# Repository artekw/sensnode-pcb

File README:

you need EAGLE 6.3.0 to open files

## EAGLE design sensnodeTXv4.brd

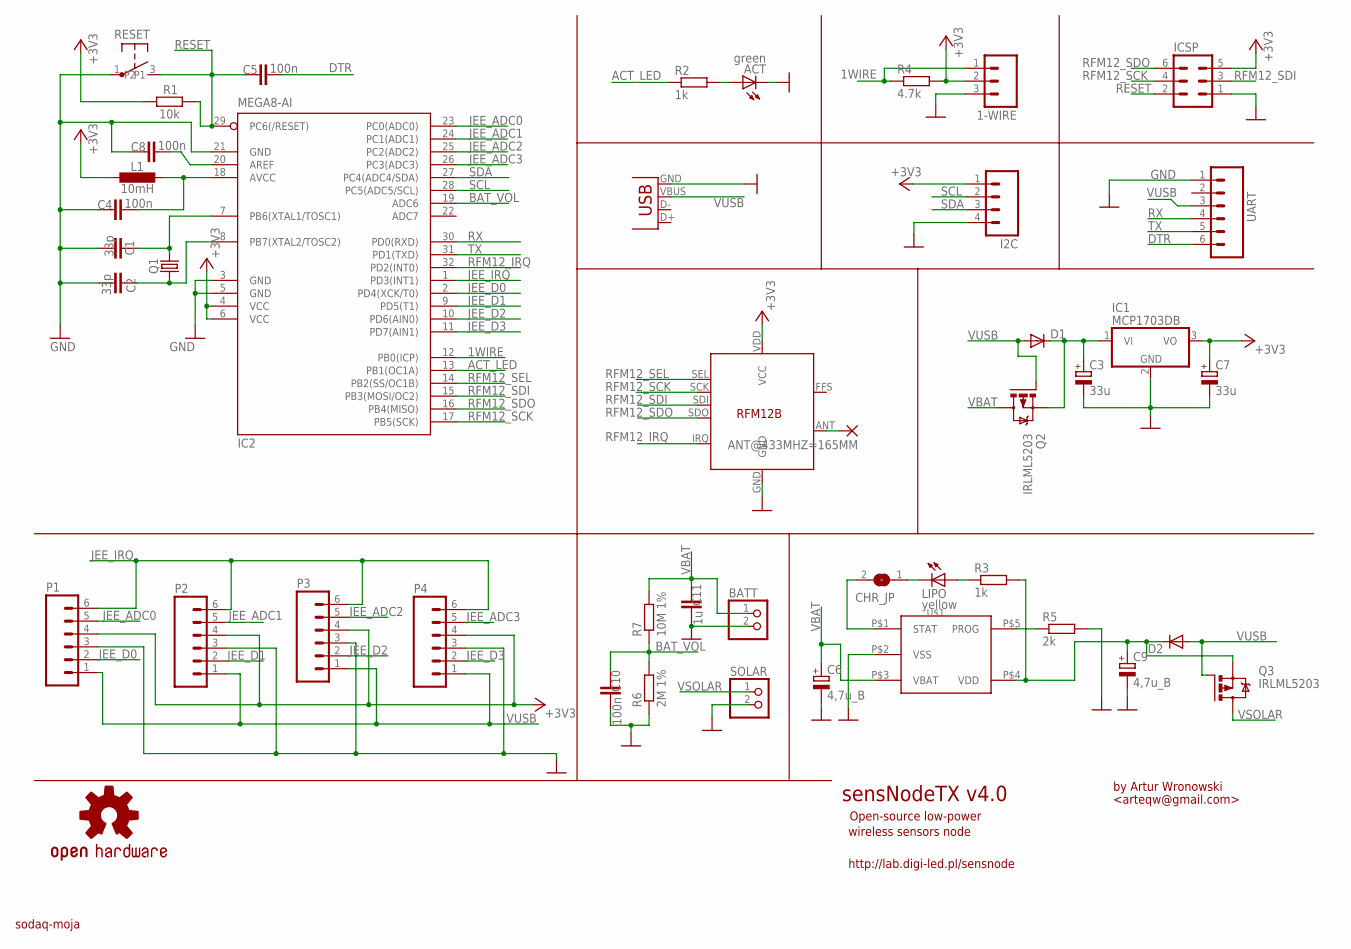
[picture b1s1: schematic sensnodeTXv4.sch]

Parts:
1-WIRE: M03LOCK; 1X03_LOCK
ACT: green; 1206
ANT@433MHZ=165MM: 2,15/1,0
BATT: PINHD-1X2; 1X02
C1, C2: 33p; C0805
C3, C7: 33u; SMC_B
C4, C5, C8, C10: 100n; C0805
C6, C9: 4,7u_B; SMC_B
C11: 1u; C0805
CHR_JP: JUMPER; SJW
D1, D2: 1n5819 melf; MELF-MLL41
I2C: M04LOCK; 1X04_LOCK
IC1: MCP1703DB; SOT223
IC2: MEGA8-AI; TQFP32-08
ICSP: MA03-2
L1: 10mH; 0207/7
LIPO: yellow; 1206
P1, P2, P3, P4: M06SIP_LOCK; 1X06-SIP_LOCK
Q1: CRYSTALHC49U70; HC49U70
Q2, Q3: IRLML5203; MICRO3
R1: 10k; M0805
R2, R3: 1k; M0805
R4: 4.7k; M0805
R5: 2k; M0805
R6: 2M 1%; M0805
R7: 10M 1%; M0805
RESET: TACT3X6; TACK3X6
RFM12B: RFM12B
SOLAR: PINHD-1X2; 1X02
U$1: MCP73831; 5PIN_SOT23
U$3: OSHW-LOGOM; OSHW-LOGO-M
UART: M06SIP_LOCK; 1X06-SIP_LOCK
USB_PWR: USBSMD; USB-MINIB

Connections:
1WIRE: 1-WIRE.1, IC2.12 (PB0(ICP)), R4.1
+3V3: 1-WIRE.2, C7.+, I2C.1, IC1.3 (VO), IC2.4 (VCC), IC2.6 (VCC), ICSP.5, L1.1, P1.4, P2.4, P3.4, P4.4, R1.1, R4.2, RFM12B.VDD (VCC)
ACT_LED: IC2.13 (PB1(OC1A)), R2.1
BAT_VOL: C10.2, IC2.19 (ADC6), R6.2, R7.1
DTR: C5.1, UART.6
GND: 1-WIRE.3, ACT.C, BATT.2, C1.2, C2.2, C3.-, C4.2, C6.-, C7.-, C8.2, C9.-, C10.1, C11.1, I2C.4, IC1.2 (GND), IC2.3 (GND), IC2.5 (GND), IC2.21 (GND), ICSP.1, P1.3, P2.3, P3.3, P4.3, R5.2, R6.1, RESET.1, RFM12B.GND, SOLAR.2, U$1.P$2 (VSS), UART.1, USB_PWR.GND
JEE_ADC0: IC2.23 (PC0(ADC0)), P1.5
JEE_ADC1: IC2.24 (PC1(ADC1)), P2.5
JEE_ADC2: IC2.25 (PC2(ADC2)), P3.5
JEE_ADC3: IC2.26 (PC3(ADC3)), P4.5
JEE_D0: IC2.2 (PD4(XCK/T0)), P1.2
JEE_D1: IC2.9 (PD5(T1)), P2.2
JEE_D2: IC2.10 (PD6(AIN0)), P3.2
JEE_D3: IC2.11 (PD7(AIN1)), P4.2
JEE_IRQ: IC2.1 (PD3(INT1)), P1.6, P2.6, P3.6, P4.6
unnamed: C2.1, IC2.8 (PB7(XTAL2/TOSC2)), Q1.1
unnamed: C1.1, IC2.7 (PB6(XTAL1/TOSC1)), Q1.2
unnamed: C4.1, IC2.18 (AVCC), L1.2
unnamed: C8.1, IC2.20 (AREF)
unnamed: LIPO.A, R3.1
unnamed: CHR_JP.2, U$1.P$1 (STAT)
unnamed: C9.+, D2.C, Q3.2 (S), R3.2, U$1.P$4 (VDD)
unnamed: ACT.A, R2.2
unnamed: R5.1, U$1.P$5 (PROG)
unnamed: CHR_JP.1, LIPO.C
unnamed: C3.+, D1.C, IC1.1 (VI), Q2.2 (S)
unnamed: ANT@433MHZ=165MM.1, RFM12B.ANT
RESET: C5.2, IC2.29 (PC6(/RESET)), ICSP.2, R1.2, RESET.3 (P2)
RFM12_IRQ: IC2.32 (PD2(INT0)), RFM12B.IRQ
RFM12_SCK: IC2.17 (PB5(SCK)), ICSP.4, RFM12B.SCK
RFM12_SDI: IC2.15 (PB3(MOSI/OC2)), ICSP.3, RFM12B.SDI
RFM12_SDO: IC2.16 (PB4(MISO)), ICSP.6, RFM12B.SDO
RFM12_SEL: IC2.14 (PB2(SS/OC1B)), RFM12B.SEL
RX: IC2.30 (PD0(RXD)), UART.4
SCL: I2C.2, IC2.28 (PC5(ADC5/SCL))
SDA: I2C.3, IC2.27 (PC4(ADC4/SDA))
TX: IC2.31 (PD1(TXD)), UART.5
VBAT: BATT.1, C6.+, C11.2, Q2.3 (D), R7.2, U$1.P$3 (VBAT)
VSOLAR: Q3.3 (D), SOLAR.1
VUSB: D1.A, D2.A, P1.1, P2.1, P3.1, P4.1, Q2.1 (G), Q3.1 (G), UART.3, USB_PWR.VBUS

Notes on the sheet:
sensNodeTX v4.0
http://lab.digi-led.pl/sensnode
by Artur Wronowski
Open-source low-power
wireless sensors node
<arteqw@gmail.com>
sodaq-moja

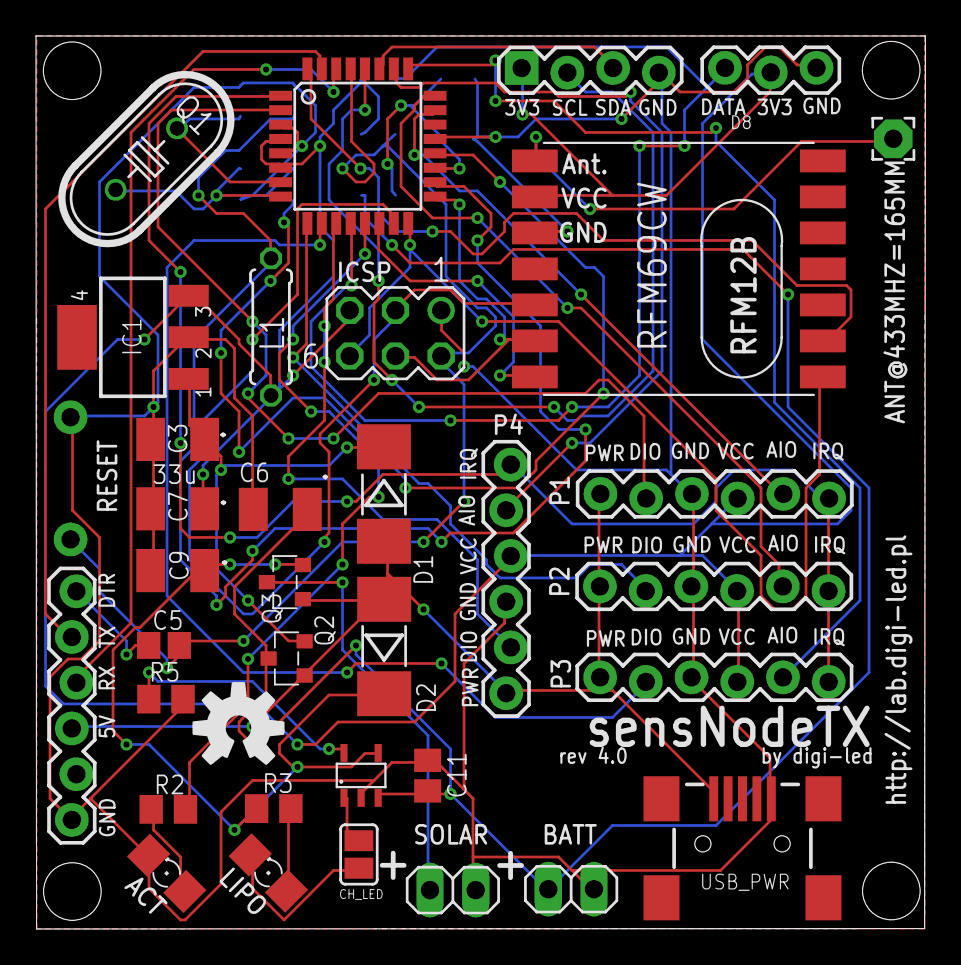
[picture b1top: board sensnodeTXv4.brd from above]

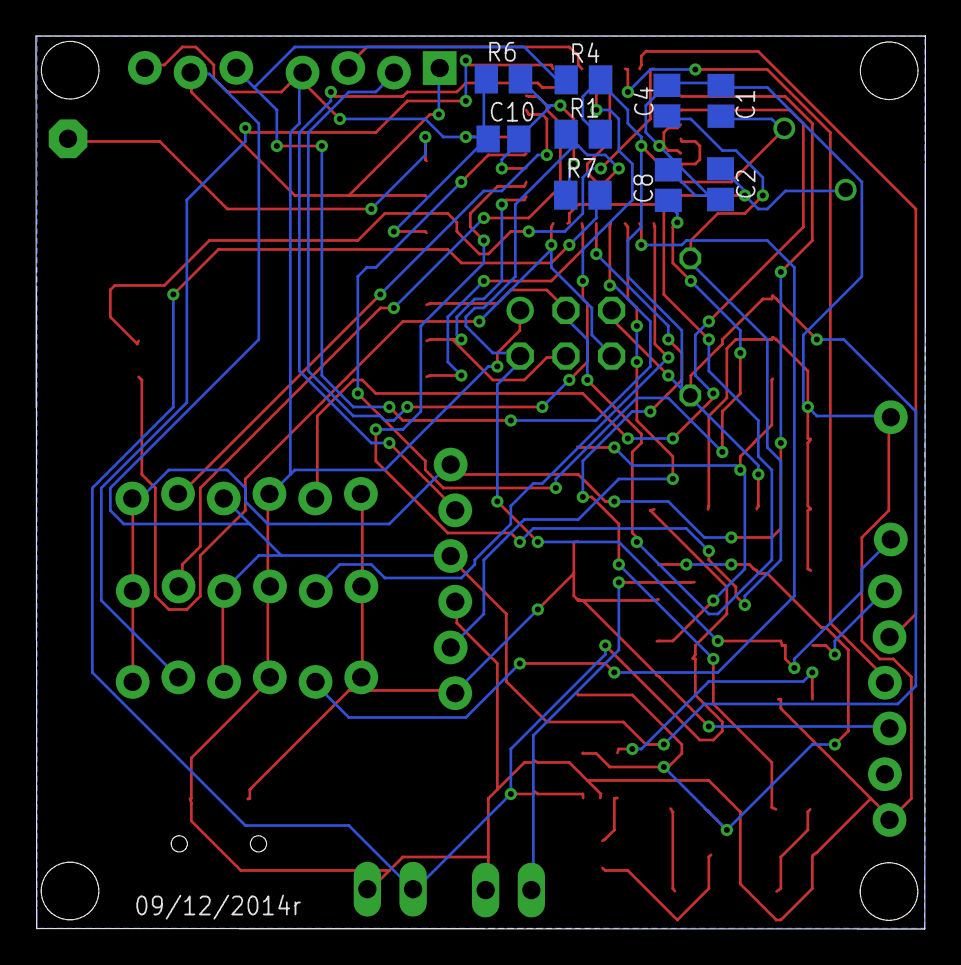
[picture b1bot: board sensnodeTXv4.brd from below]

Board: 2 copper layers, 49.4 x 49.6 mm, 45 parts (9 on the bottom side), 40 nets.

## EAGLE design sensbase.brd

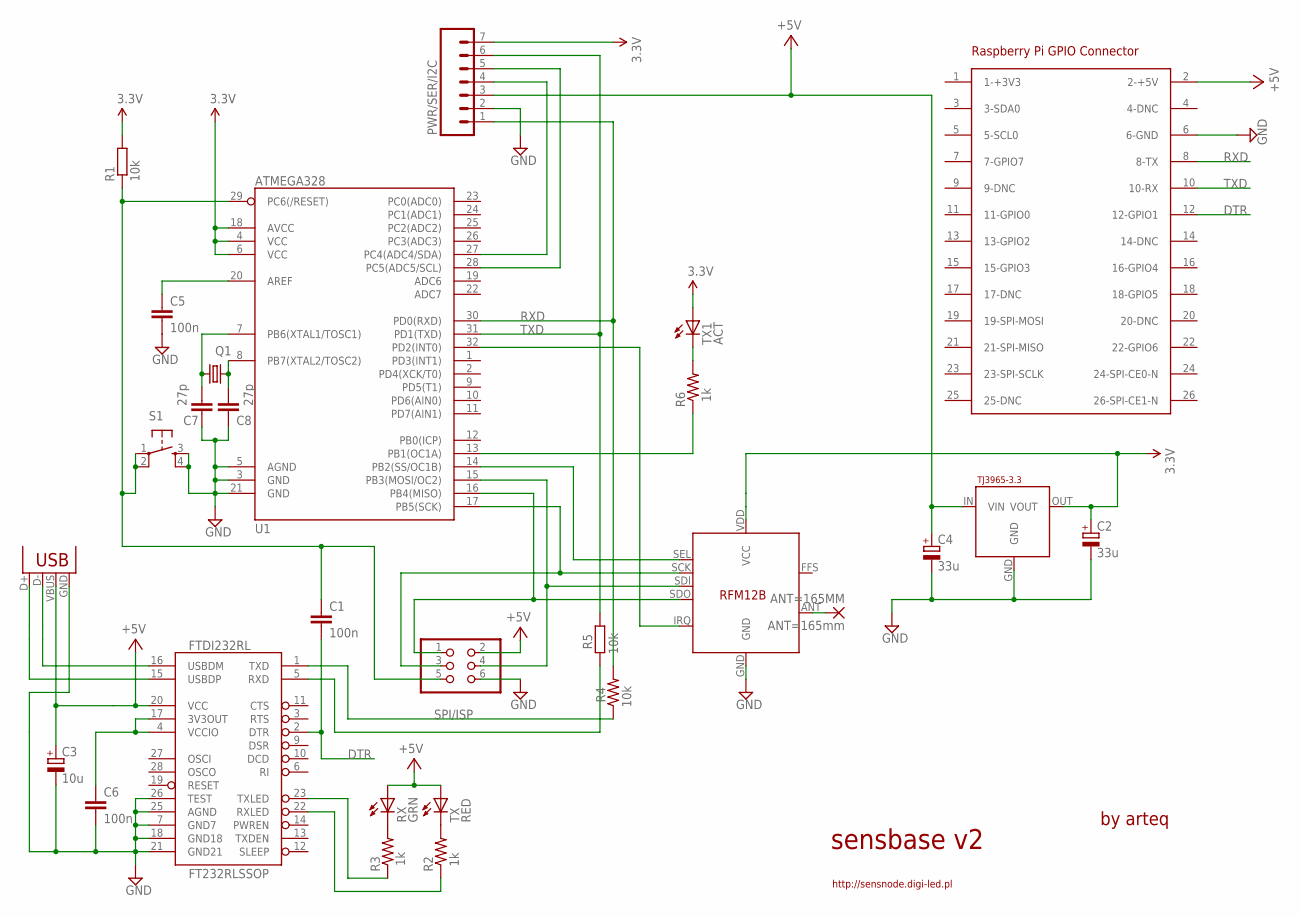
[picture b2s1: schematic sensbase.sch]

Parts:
3.3: TJ3965-3.3; SOT223
ANT=165MM: ANT=165mm; 1,6/0,9
C1, C5, C6: 100n; C0805
C2, C4: 33u; SMC_B
C3: 10u; SMC_A
C7, C8: 27p; C0805
FTDI232RL: FT232RLSSOP; SSOP28DB
PWR/SER/I2C: PSI; 1X07
Q1: CRYSTALHC49UP; HC49UP
R1, R5: 10k; R0805
R2, R3, R6: 1k; R0805@1
R4: 10k; R0805@1
RF433: RFM12B
RX: GRN; CHIP-LED0805
S1: TAC_SWITCHSMD; TACTILE_SWITCH_SMD
SV7: SPI/ISP; 2X03
TX: RED; CHIP-LED0805
TX1: ACT; CHIP-LED0805
U1: ATMEGA328; TQFP32-08
U$2: RASPBERRY-PI
X1: USBSMD; USB-MINIB

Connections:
+5V: 3.3.IN (VIN), C3.+, C4.+, FTDI232RL.20 (VCC), PWR/SER/I2C.3, RX.A, SV7.2, TX.A, U$2.2 (2-+5V), X1.VBUS
DTR: C1.2, FTDI232RL.2 (DTR), U$2.12 (12-GPIO1)
GND: 3.3.GND, C2.-, C3.-, C4.-, C5.2, C6.2, C7.2, C8.2, FTDI232RL.7 (GND7), FTDI232RL.18 (GND18), FTDI232RL.21 (GND21), FTDI232RL.25 (AGND), FTDI232RL.26 (TEST), PWR/SER/I2C.2, RF433.GND, S1.3, S1.4, SV7.6, U1.3 (GND), U1.5 (AGND), U1.21 (GND), U$2.6 (6-GND), X1.GND
unnamed: C7.1, Q1.1, U1.7 (PB6(XTAL1/TOSC1))
unnamed: RF433.SDO, SV7.1, U1.16 (PB4(MISO))
unnamed: RF433.SDI, SV7.4, U1.15 (PB3(MOSI/OC2))
unnamed: RF433.SEL, U1.14 (PB2(SS/OC1B))
unnamed: RF433.SCK, SV7.3, U1.17 (PB5(SCK))
unnamed: R6.1, U1.13 (PB1(OC1A))
unnamed: RF433.IRQ, U1.32 (PD2(INT0))
unnamed: C1.1, R1.1, S1.1, S1.2, SV7.5, U1.29 (PC6(/RESET))
unnamed: C5.1, U1.20 (AREF)
unnamed: R6.2, TX1.C
unnamed: FTDI232RL.16 (USBDM), X1.D-
unnamed: FTDI232RL.15 (USBDP), X1.D+
unnamed: FTDI232RL.1 (TXD), R4.1
unnamed: ANT=165MM.1, RF433.ANT
unnamed: C6.1, FTDI232RL.4 (VCCIO), FTDI232RL.17 (3V3OUT)
unnamed: C8.1, Q1.2, U1.8 (PB7(XTAL2/TOSC2))
unnamed: PWR/SER/I2C.5, U1.28 (PC5(ADC5/SCL))
unnamed: PWR/SER/I2C.4, U1.27 (PC4(ADC4/SDA))
unnamed: R2.2, TX.C
unnamed: R3.2, RX.C
unnamed: FTDI232RL.23 (TXLED), R3.1
unnamed: FTDI232RL.22 (RXLED), R2.1
RXD: PWR/SER/I2C.1, R4.2, U1.30 (PD0(RXD)), U$2.8 (8-TX)
TXD: PWR/SER/I2C.6, R5.2, U1.31 (PD1(TXD)), U$2.10 (10-RX)
TXD1: FTDI232RL.5 (RXD), R5.1
VCC: 3.3.OUT (VOUT), C2.+, PWR/SER/I2C.7, R1.2, RF433.VDD (VCC), TX1.A, U1.4 (VCC), U1.6 (VCC), U1.18 (AVCC)

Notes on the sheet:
sensbase v2
by arteq
http://sensnode.digi-led.pl
Raspberry Pi GPIO Connector

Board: 2 copper layers, 29 parts (0 on the bottom side), 29 nets, no tracks yet.

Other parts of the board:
U$1: OSHW-LOGO-M

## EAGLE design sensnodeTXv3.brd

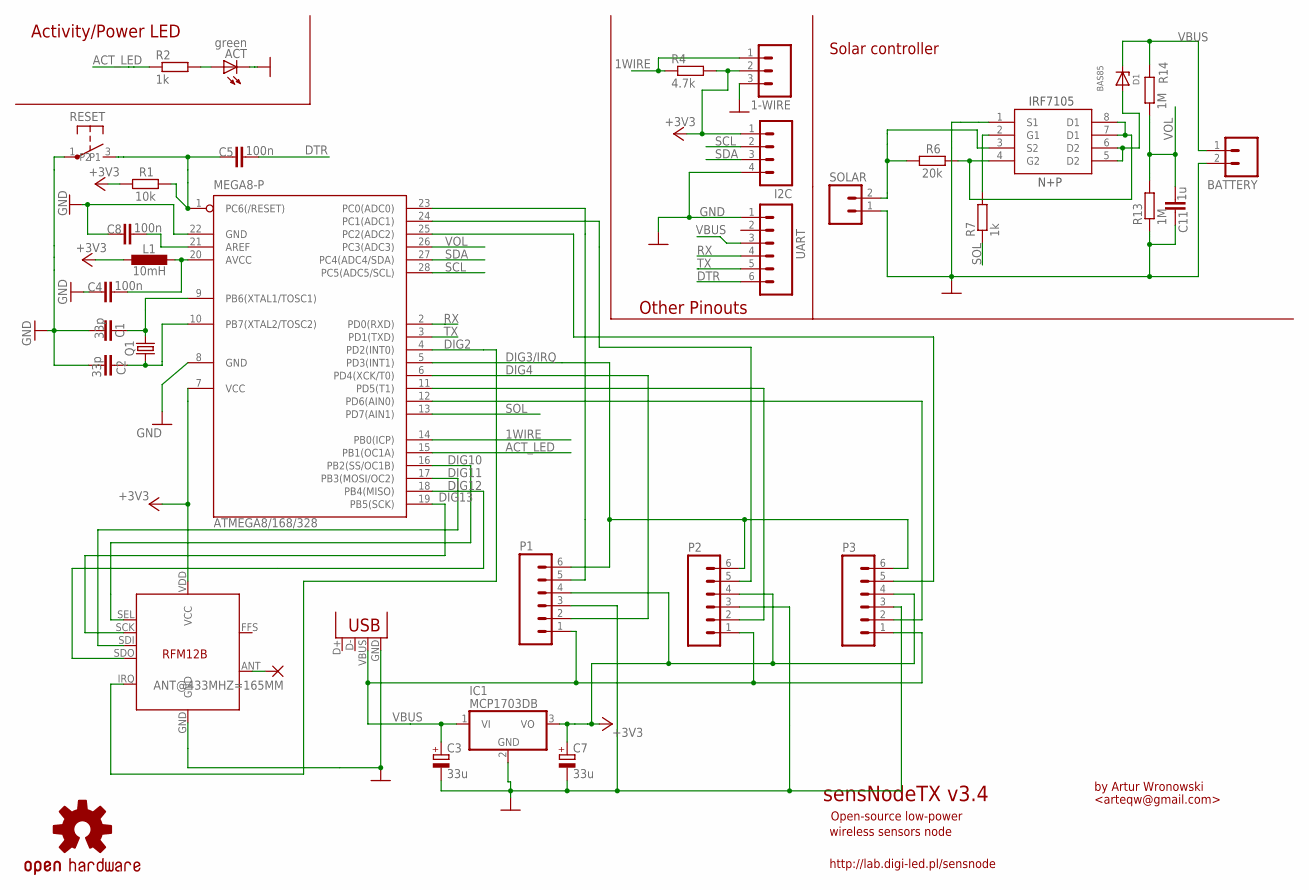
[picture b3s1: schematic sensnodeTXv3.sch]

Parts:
1-WIRE: M03LOCK; 1X03_LOCK
ACT: green; 1206
ANT@433MHZ=165MM: 2,15/1,0
ATMEGA8/168/328: MEGA8-P; DIL28-3
BATTERY: M02LOCK; 1X02_LOCK
C1, C2: 33p; C0805
C3, C7: 33u; SMC_B
C4, C5, C8: 100n; C0805
C11: 1u; C0805
D1: BAS85; SOD80C
I2C: M04LOCK; 1X04_LOCK
IC1: MCP1703DB; SOT223
L1: 10mH; 0207/7
P1, P2, P3: M06SIP_LOCK; 1X06-SIP_LOCK
Q1: CRYSTALHC49U70; HC49U70
R1: 10k; M0805
R2, R7: 1k; M0805
R4: 4.7k; M0805
R6: 20k; M0805
R13, R14: 1M; M0805
RESET: TACT3X6; TACK3X6
RFM12B: RFM12B
SOLAR: M02LOCK; 1X02_LOCK
U$3: OSHW-LOGOM; OSHW-LOGO-M
U$4: IRF7105; SO8
UART: M06SIP_LOCK; 1X06-SIP_LOCK
USB_PWR: USBSMD; USB-MINIB

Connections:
1WIRE: 1-WIRE.1, ATMEGA8/168/328.14 (PB0(ICP)), R4.1
+3V3: 1-WIRE.2, ATMEGA8/168/328.7 (VCC), C7.+, I2C.1, IC1.3 (VO), L1.1, P1.4, P2.4, P3.4, R1.1, R4.2, RFM12B.VDD (VCC)
ACT_LED: ATMEGA8/168/328.15 (PB1(OC1A)), R2.1
DIG2: ATMEGA8/168/328.4 (PD2(INT0)), RFM12B.IRQ
DIG3/IRQ: ATMEGA8/168/328.5 (PD3(INT1)), P1.6, P2.6, P3.6
DIG4: ATMEGA8/168/328.6 (PD4(XCK/T0)), P1.2
DIG10: ATMEGA8/168/328.16 (PB2(SS/OC1B)), RFM12B.SEL
DIG11: ATMEGA8/168/328.17 (PB3(MOSI/OC2)), RFM12B.SDI
DIG12: ATMEGA8/168/328.18 (PB4(MISO)), RFM12B.SDO
DIG13: ATMEGA8/168/328.19 (PB5(SCK)), RFM12B.SCK
DTR: C5.1, UART.6
GND: 1-WIRE.3, ACT.C, ATMEGA8/168/328.8 (GND), ATMEGA8/168/328.22 (GND), BATTERY.2, C1.2, C2.2, C3.-, C4.2, C7.-, C8.2, C11.2, I2C.4, IC1.2 (GND), P1.3, P2.3, P3.3, R13.1, RESET.1, RFM12B.GND, SOLAR.1, U$4.1 (S1), UART.1, USB_PWR.GND
unnamed: ATMEGA8/168/328.10 (PB7(XTAL2/TOSC2)), C2.1, Q1.1
unnamed: ATMEGA8/168/328.9 (PB6(XTAL1/TOSC1)), C1.1, Q1.2
unnamed: ATMEGA8/168/328.20 (AVCC), C4.1, L1.2
unnamed: ATMEGA8/168/328.21 (AREF), C8.1
unnamed: ATMEGA8/168/328.25 (PC2(ADC2)), P3.5
unnamed: D1.A, U$4.5 (D2), U$4.6 (D2)
unnamed: ATMEGA8/168/328.11 (PD5(T1)), P2.2
unnamed: ACT.A, R2.2
unnamed: ATMEGA8/168/328.12 (PD6(AIN0)), P3.2
unnamed: ATMEGA8/168/328.24 (PC1(ADC1)), P2.5
unnamed: R6.1, SOLAR.2, U$4.3 (S2)
unnamed: R7.2, U$4.2 (G1)
unnamed: ATMEGA8/168/328.23 (PC0(ADC0)), P1.5
unnamed: R6.2, U$4.4 (G2), U$4.7 (D1), U$4.8 (D1)
unnamed: ANT@433MHZ=165MM.1, RFM12B.ANT
P2: ATMEGA8/168/328.1 (PC6(/RESET)), C5.2, R1.2, RESET.3 (P2)
RX: ATMEGA8/168/328.2 (PD0(RXD)), UART.4
SCL: ATMEGA8/168/328.28 (PC5(ADC5/SCL)), I2C.2
SDA: ATMEGA8/168/328.27 (PC4(ADC4/SDA)), I2C.3
SOL: ATMEGA8/168/328.13 (PD7(AIN1)), R7.1
TX: ATMEGA8/168/328.3 (PD1(TXD)), UART.5
VBUS: BATTERY.1, C3.+, D1.C, IC1.1 (VI), P1.1, P2.1, P3.1, R14.2, UART.3, USB_PWR.VBUS
VOL: ATMEGA8/168/328.26 (PC3(ADC3)), C11.1, R13.2, R14.1

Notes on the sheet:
sensNodeTX v3.4
http://lab.digi-led.pl/sensnode
by Artur Wronowski
Solar controller
Activity/Power LED
Open-source low-power
wireless sensors node
Other Pinouts
<arteqw@gmail.com>
IRF7105
N+P

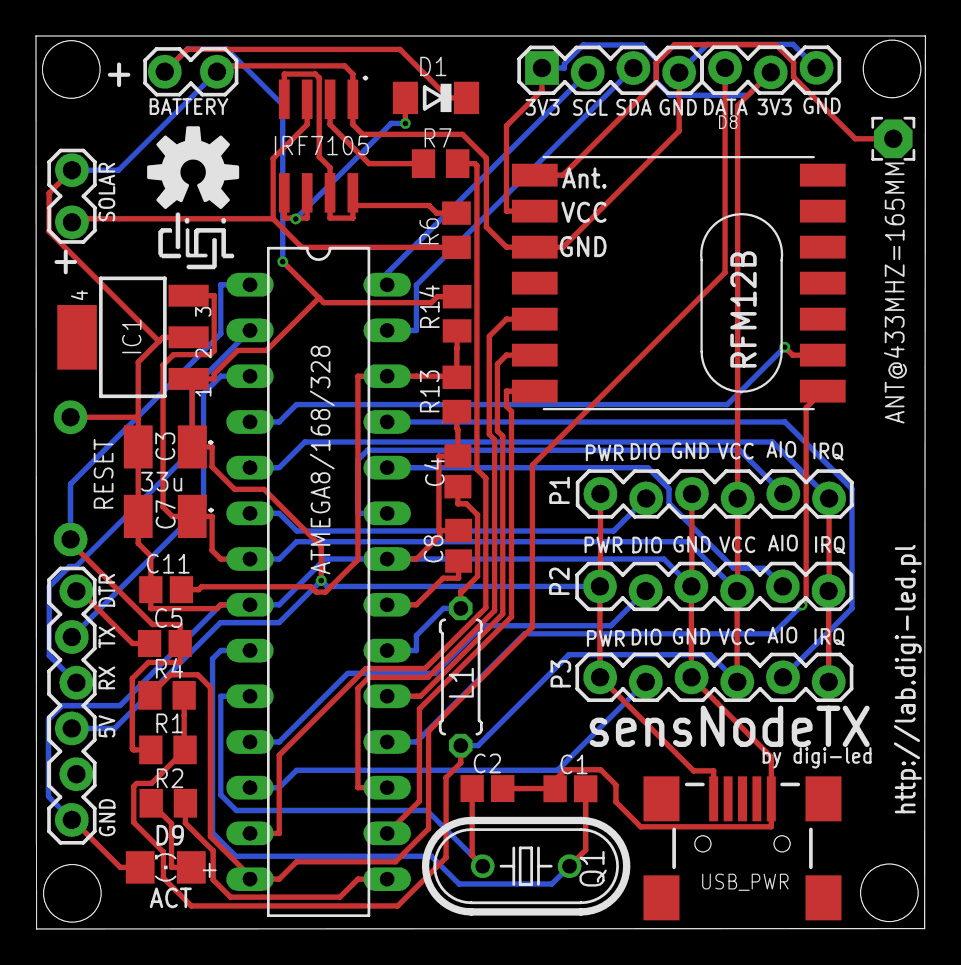
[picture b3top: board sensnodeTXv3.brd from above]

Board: 2 copper layers, 49.4 x 49.6 mm, 35 parts (0 on the bottom side), 35 nets.

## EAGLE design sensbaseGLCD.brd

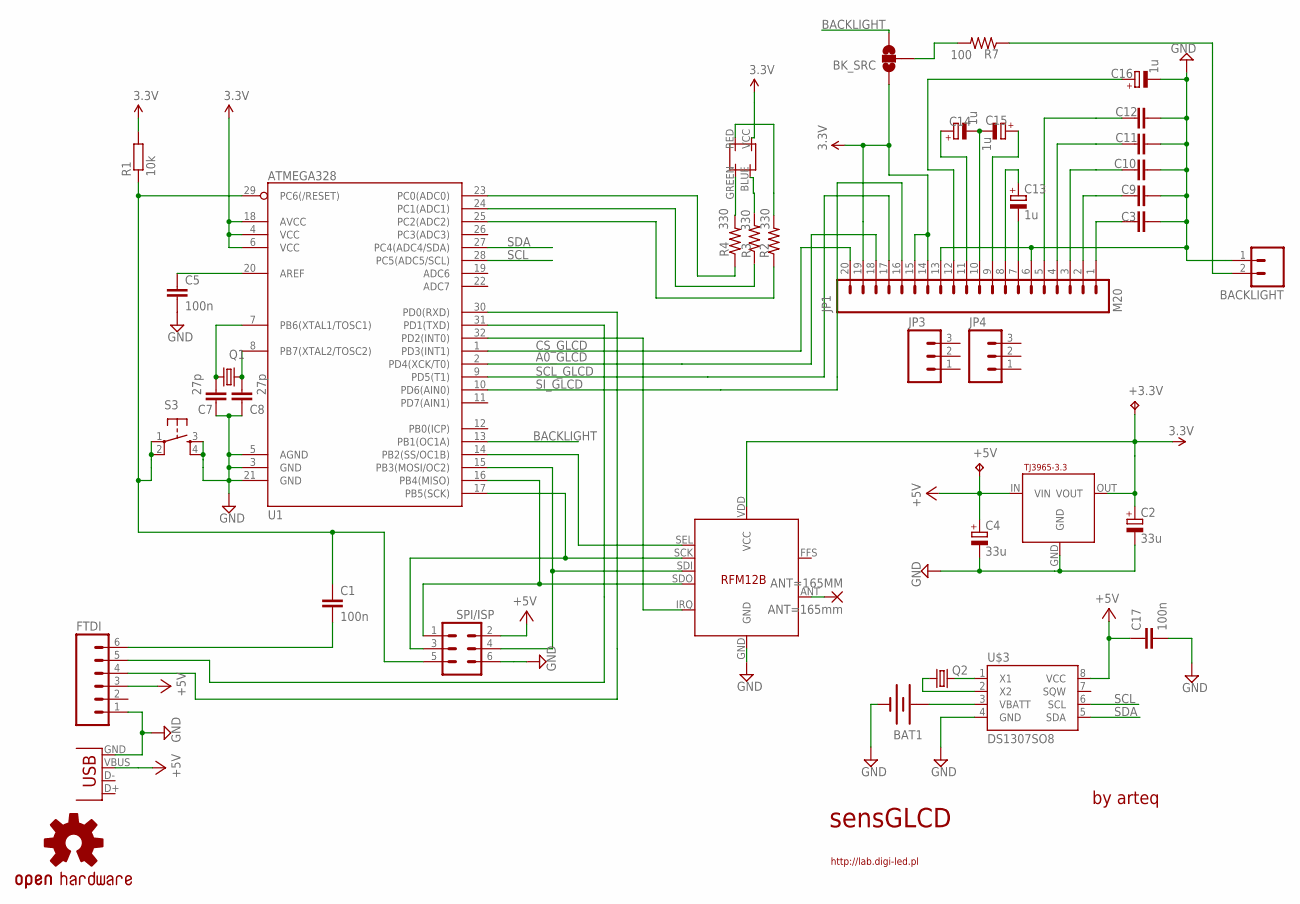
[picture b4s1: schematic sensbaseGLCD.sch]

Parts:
3.3: TJ3965-3.3; SOT223
+3.3V, +5V: TPB1,27; B1,27
ANT=165MM: ANT=165mm; 2,15/1,0
BACKLIGHT: M02PTH; 1X02
BAT1: BATTERY20PTH; BATTCOM_20MM_PTH
BK_SRC: SOLDERJUMPER_2WAYT; SJ_2
C1, C5, C17: 100n; C0805
C2, C4: 33u; SMC_B
C3, C9, C10, C11, C12: 1u; C0805
C7, C8: 27p; C0805
C13, C14, C15, C16: 1u; A/3216-18R
FTDI: M06SIP; 1X06
JP1: M20; 1X20
JP3, JP4: M03PTH; 1X03
Q1: CRYSTALHC49UP; HC49UP
Q2: CRYSTALTC26H; TC26H
R1: 10k; R0805
R2, R3, R4: 330; R0805
R7: 100; R0805
RF433: RFM12B
S3: TAC_SWITCHSMD; TACTILE_SWITCH_SMD
SV7: SPI/ISP; MA03-2
U1: ATMEGA328; TQFP32-08
U$2: OSHW-LOGOL; OSHW-LOGO-L
U$3: DS1307SO8; SO08
U$4: RGB1206
X1: USBSMD; USB-MINIB

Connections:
+5V: 3.3.IN (VIN), +5V.TP, C4.+, C17.1, FTDI.3, SV7.2, U$3.8 (VCC), X1.VBUS
A0_GLCD: JP1.18, U1.2 (PD4(XCK/T0))
BACKLIGHT: BK_SRC.3, U1.13 (PB1(OC1A))
CS_GLCD: JP1.20, U1.1 (PD3(INT1))
GND: 3.3.GND, BACKLIGHT.1, BAT1.2 (-), C2.-, C3.2, C4.-, C5.2, C7.2, C8.2, C9.2, C10.2, C11.2, C12.2, C16.-, C17.2, FTDI.1, JP1.6, JP1.13, RF433.GND, S3.3, S3.4, SV7.6, U1.3 (GND), U1.5 (AGND), U1.21 (GND), U$3.4 (GND), X1.GND
unnamed: C7.1, Q1.1, U1.7 (PB6(XTAL1/TOSC1))
unnamed: RF433.SDO, SV7.1, U1.16 (PB4(MISO))
unnamed: RF433.SDI, SV7.4, U1.15 (PB3(MOSI/OC2))
unnamed: RF433.SEL, U1.14 (PB2(SS/OC1B))
unnamed: RF433.SCK, SV7.3, U1.17 (PB5(SCK))
unnamed: R4.2, U$4.GREEN (GR)
unnamed: RF433.IRQ, U1.32 (PD2(INT0))
unnamed: C1.2, FTDI.6
unnamed: R2.2, U$4.RED (RE)
unnamed: R3.2, U$4.BLUE (BL)
unnamed: C5.1, U1.20 (AREF)
unnamed: BAT1.1 (+), U$3.3 (VBATT)
unnamed: C1.1, R1.1, S3.1, S3.2, SV7.5, U1.29 (PC6(/RESET))
unnamed: C14.-, C15.-, JP1.10
unnamed: Q2.2, U$3.2 (X2)
unnamed: Q2.1, U$3.1 (X1)
unnamed: ANT=165MM.1, RF433.ANT
unnamed: C12.1, JP1.5
unnamed: BK_SRC.2, R7.2
unnamed: C8.1, Q1.2, U1.8 (PB7(XTAL2/TOSC2))
unnamed: C3.1, JP1.1
unnamed: C13.+, JP1.8
unnamed: C13.-, JP1.7
unnamed: R4.1, U1.23 (PC0(ADC0))
unnamed: R3.1, U1.24 (PC1(ADC1))
unnamed: R2.1, U1.25 (PC2(ADC2))
unnamed: C14.+, JP1.11
unnamed: C15.+, JP1.9
unnamed: C16.+, JP1.12
unnamed: BACKLIGHT.2, R7.1
unnamed: C9.1, JP1.2
unnamed: C10.1, JP1.3
unnamed: C11.1, JP1.4
RXD: FTDI.4, U1.30 (PD0(RXD))
SCL: U1.28 (PC5(ADC5/SCL)), U$3.6 (SCL)
SCL_GLCD: JP1.17, U1.9 (PD5(T1))
SDA: U1.27 (PC4(ADC4/SDA)), U$3.5 (SDA)
SI_GLCD: JP1.16, U1.10 (PD6(AIN0))
TXD: FTDI.5, U1.31 (PD1(TXD))
VCC: 3.3.OUT (VOUT), +3.3V.TP, BK_SRC.1, C2.+, JP1.14, JP1.15, JP1.19, R1.2, RF433.VDD (VCC), U1.4 (VCC), U1.6 (VCC), U1.18 (AVCC), U$4.VCC

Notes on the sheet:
sensGLCD
by arteq
http://lab.digi-led.pl

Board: 2 copper layers, 42 parts (1 on the bottom side), 45 nets, no tracks yet.

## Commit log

2011-10-23 add sensbaseGLCD pcb
2012-04-21 Aktualne schematy
2012-07-12 sensnode update
2012-11-30 update sensbaseGLSD and sensndoeTX
2012-11-30 need latest Eagle
2014-05-02 update sensnodeTX and sensbase
2014-05-02 fix image
2014-05-02 rm image
2014-05-02 add image
2015-08-16 sensnodeTXv4
